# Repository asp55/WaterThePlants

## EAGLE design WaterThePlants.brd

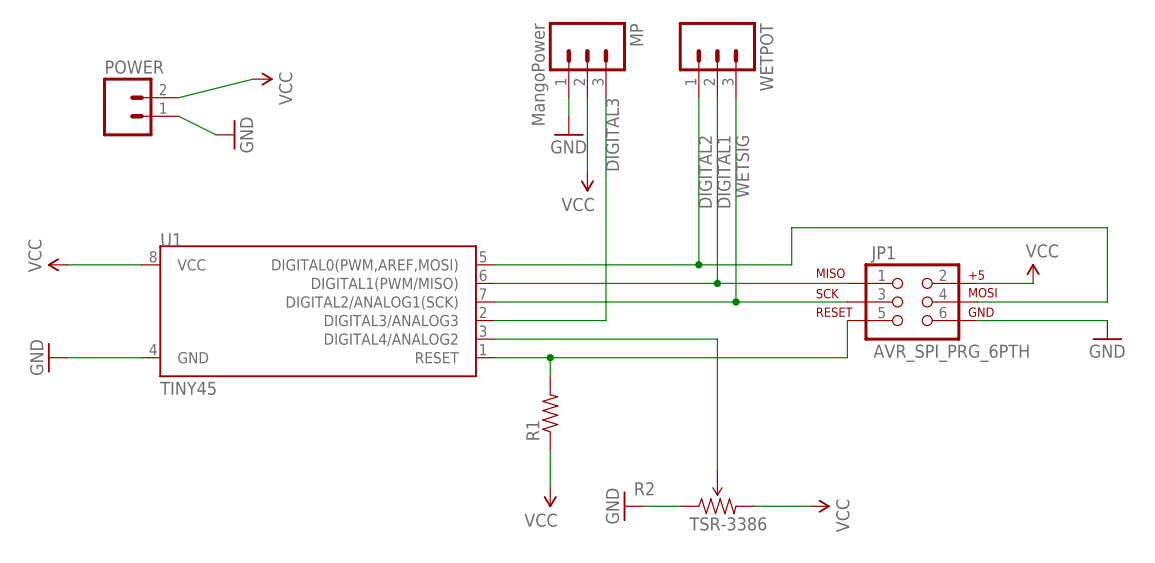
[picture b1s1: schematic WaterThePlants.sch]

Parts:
JP1: AVR_SPI_PRG_6PTH; 2X3
MP: MangoPower; 1X03
POWER: M02POLAR; MOLEX-1X2
R1: RESISTORAXIAL-0.3; AXIAL-0.3
R2: TSR-3386; 3362U-2
U1: TINY45; DIP08
WETPOT: M03PTH; 1X03

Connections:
DIGITAL1: JP1.1, U1.6 (DIGITAL1(PWM/MISO)), WETPOT.2
DIGITAL2: JP1.4, U1.5 (DIGITAL0(PWM,AREF,MOSI)), WETPOT.1
DIGITAL3: MP.3, U1.2 (DIGITAL3/ANALOG3)
GND: JP1.6, MP.1, POWER.1, R2.1 (CCW), U1.4 (GND)
unnamed: R2.2 (WIPER), U1.3 (DIGITAL4/ANALOG2)
unnamed: JP1.5, R1.P$2 (2), U1.1 (RESET)
VCC: JP1.2, MP.2, POWER.2, R1.P$1 (1), R2.3 (CW), U1.8 (VCC)
WETSIG: JP1.3, U1.7 (DIGITAL2/ANALOG1(SCK)), WETPOT.3

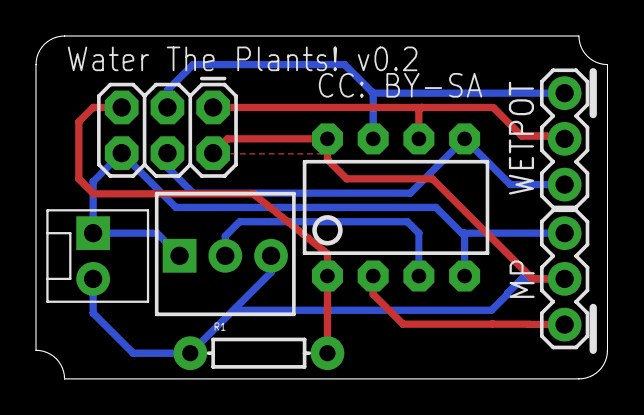
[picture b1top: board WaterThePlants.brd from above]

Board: 2 copper layers, 31.8 x 19.1 mm, 7 parts (0 on the bottom side), 8 nets.

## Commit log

2015-04-16 Created schematic and board. Added trimpot to allow on the fly calibration.
2015-04-26 Fixed so wetpot is reading on an analog pin. Updated to v0.2

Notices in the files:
parts and their libraries:
SparkFun-Connectors: Licensing: Creative Commons ShareAlike 4.0 International - https://creativecommons.org/licenses/by-sa/4.0
